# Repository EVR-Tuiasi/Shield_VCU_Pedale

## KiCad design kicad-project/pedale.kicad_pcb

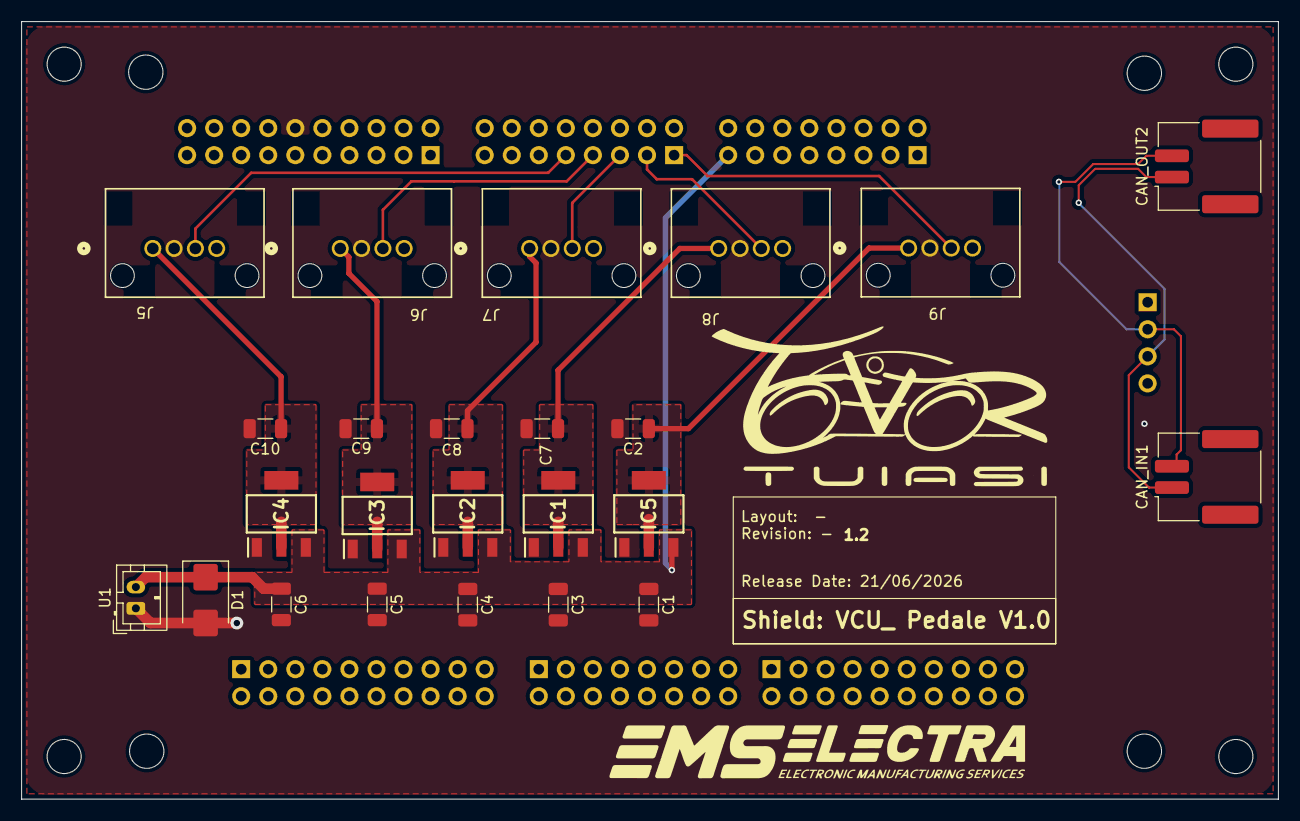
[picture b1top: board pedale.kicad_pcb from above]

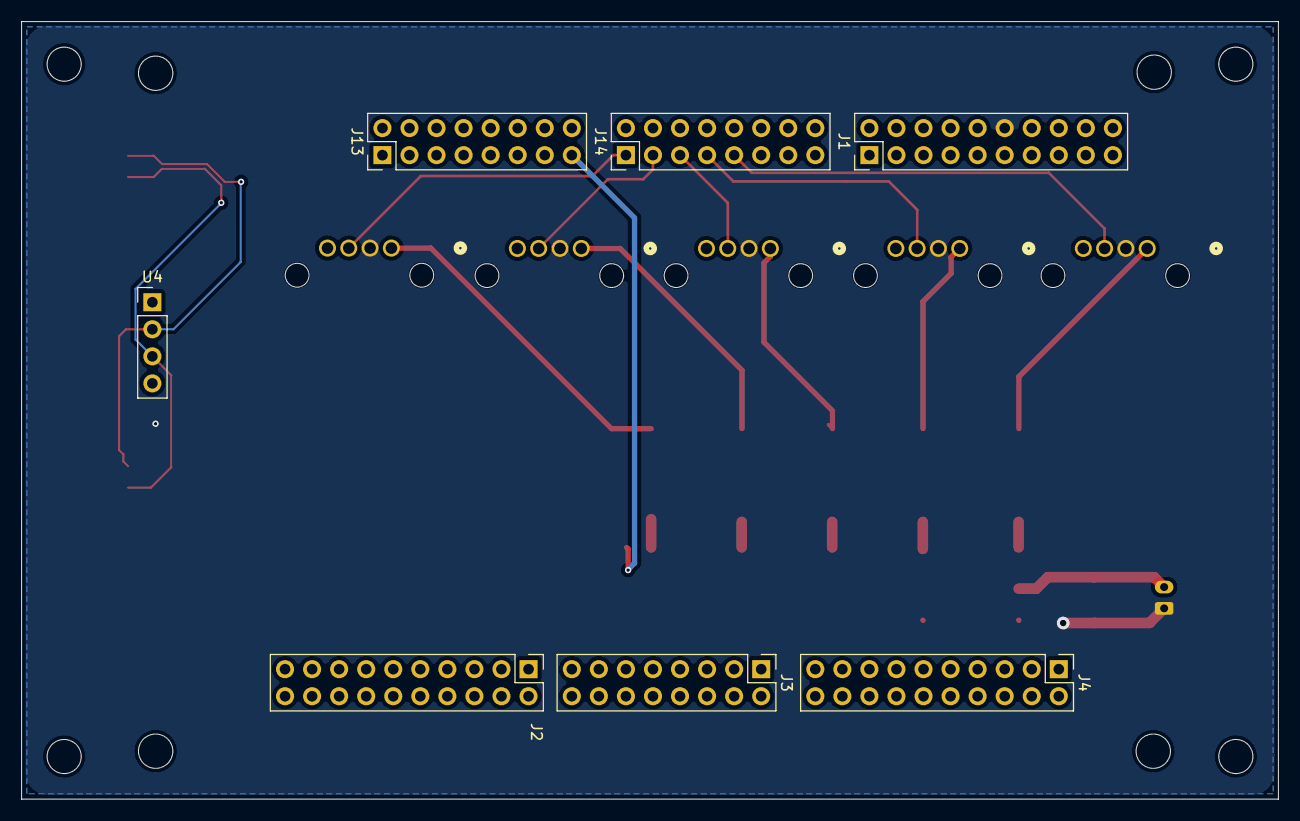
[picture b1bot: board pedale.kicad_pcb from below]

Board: 2 copper layers, 118.0 x 73.0 mm, 31 parts (7 on the bottom side), 14 nets.

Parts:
C1, C3, C4, C5, C6: 1μF; C_1206_3216Metric
C2, C7, C8, C9, C10: 2.2μF; C_1206_3216Metric
CAN_IN1: Molex_DuraClik_502352-0200_1x02-1MP_P2.00mm_Horizontal
CAN_OUT2: Molex_DuraClik_502352-0200_1x02-1MP_P2.00mm_Horizontal
D1: SS32; D_SMB
IC1, IC2, IC3, IC4, IC5: TLV76150DCYR; SOT230P700X180-4N
J1, J2, J4: PinHeader_2x10_P2.54mm_Vertical
J3, J13, J14: PinHeader_2x08_P2.54mm_Vertical
J5, J6, J7, J8, J9: 347920040; CONN_SD-34792-001_04_MOL
U1: JST_PH_B2B-PH-K_1x02_P2.00mm_Vertical
U4: PinHeader_1x04_P2.54mm_Vertical

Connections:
12V: C1.1, C3.1, C4.1, C5.1, C6.1, D1.1 (K), IC1.3 (IN), IC2.3 (IN), IC3.3 (IN), IC4.3 (IN), IC5.3 (IN), J13.15 (VBAT_15), U1.2 (12V)
/5V_1: C10.1, IC4.2 (OUT_1), IC4.4 (OUT_2), J5.1
/5V_2: C9.1, IC3.2 (OUT_1), IC3.4 (OUT_2), J6.1
/5V_3: C8.1, IC2.2 (OUT_1), IC2.4 (OUT_2), J7.1
/5V_4: C7.1, IC1.2 (OUT_1), IC1.4 (OUT_2), J8.1
/5V_5: C2.1, IC5.2 (OUT_1), IC5.4 (OUT_2), J9.1
/CAN_N: CAN_IN1.2 (CANL), CAN_OUT2.2 (CANL), U4.2 (CANL)
/CAN_P: CAN_IN1.1 (CANH), CAN_OUT2.1 (CANH), U4.3 (CANH)
/Senzor_poz_1: J6.3, J14.7 (pta8)
/Senzor_poz_2: J7.3, J14.5 (pta13)
/Senzor_poz_3: J8.3, J14.3 (ptd0)
/Senzor_poz_4: J9.3, J14.1 (ptd1)
/Senzor_presiune: J5.3, J14.9 (pta9)
GND: C1.2, C2.2, C3.2, C4.2, C5.2, C6.2, C7.2, C8.2, C9.2, C10.2, D1.2 (A), IC1.1 (GND), IC2.1 (GND), IC3.1 (GND), IC4.1 (GND), IC5.1 (GND), J1.12 (GND_12), J5.2, J6.2, J7.2, J8.2, J9.2, U1.1 (GND)

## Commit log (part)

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2026-03-18 Adaugat proiect kicad
2026-03-19 modificari
2026-03-22 modificari 2
2026-03-23 Schimbari dupa sugestii noi
2026-03-23 modificari aplicate
2026-03-24 modificari 3
2026-03-26 trebuie sa verific/schimb conectorii sa aiba pinii buni
2026-03-26 modificari 4
2026-03-26 viorel checked
2026-05-06 step file
2026-06-14 CAN_IN + CAN_OUT - added
2026-06-20 V_divirders removed+ Connectors moved
2026-06-20 GND on Diode placed
2026-06-21 Logos added (EMS/EVR)
2026-06-21 added exclude tracks area for diode
2026-06-21 Fix for unwanted GND connection
2026-06-21 Fixed 3 drc errors
2026-06-25 Fix one DRC warning for silkscreen
2026-06-26 Removed custom GND from supply connector
2026-06-29 GBR added
